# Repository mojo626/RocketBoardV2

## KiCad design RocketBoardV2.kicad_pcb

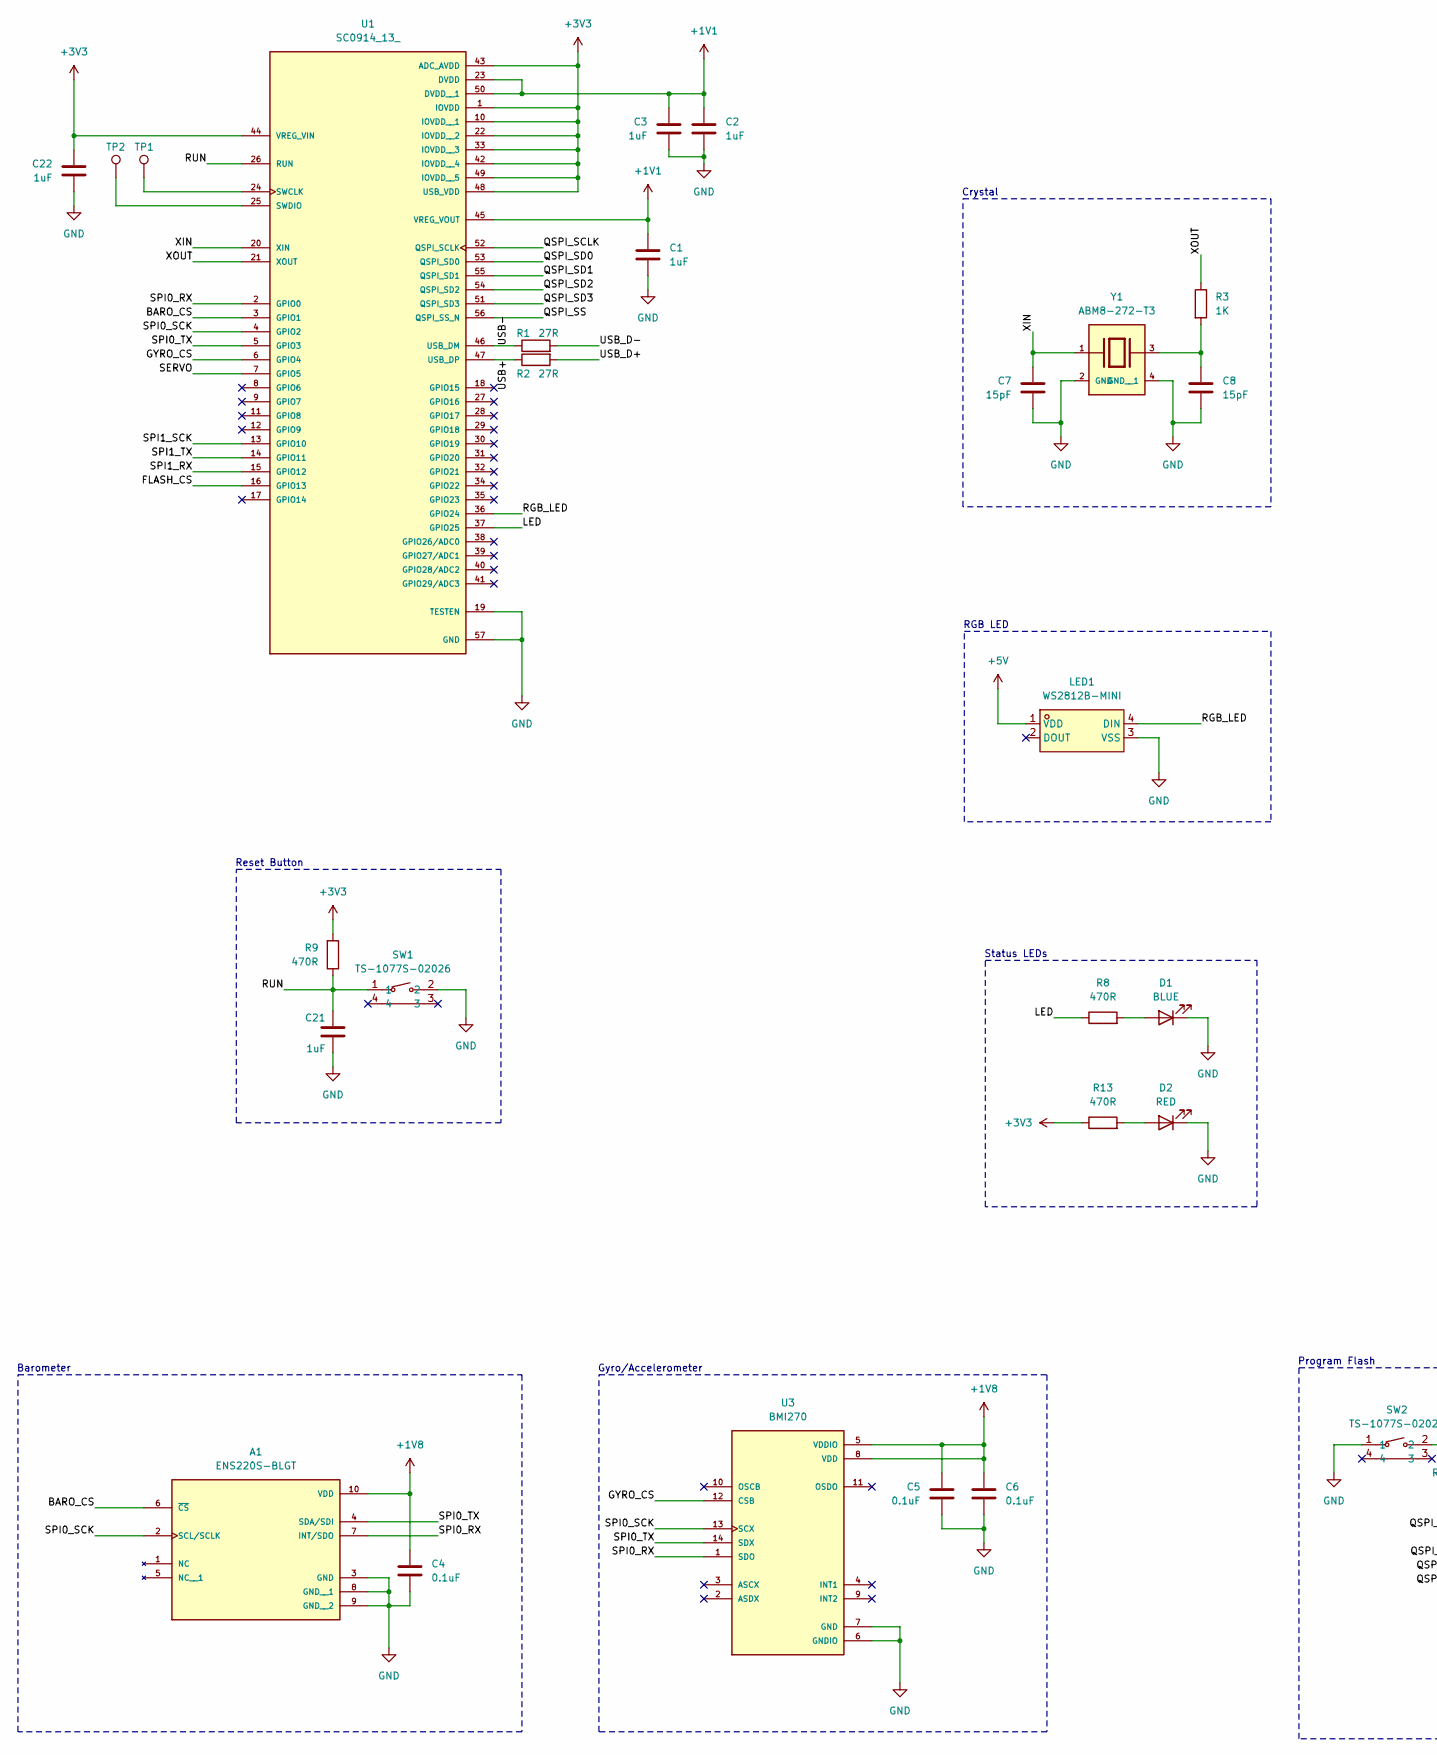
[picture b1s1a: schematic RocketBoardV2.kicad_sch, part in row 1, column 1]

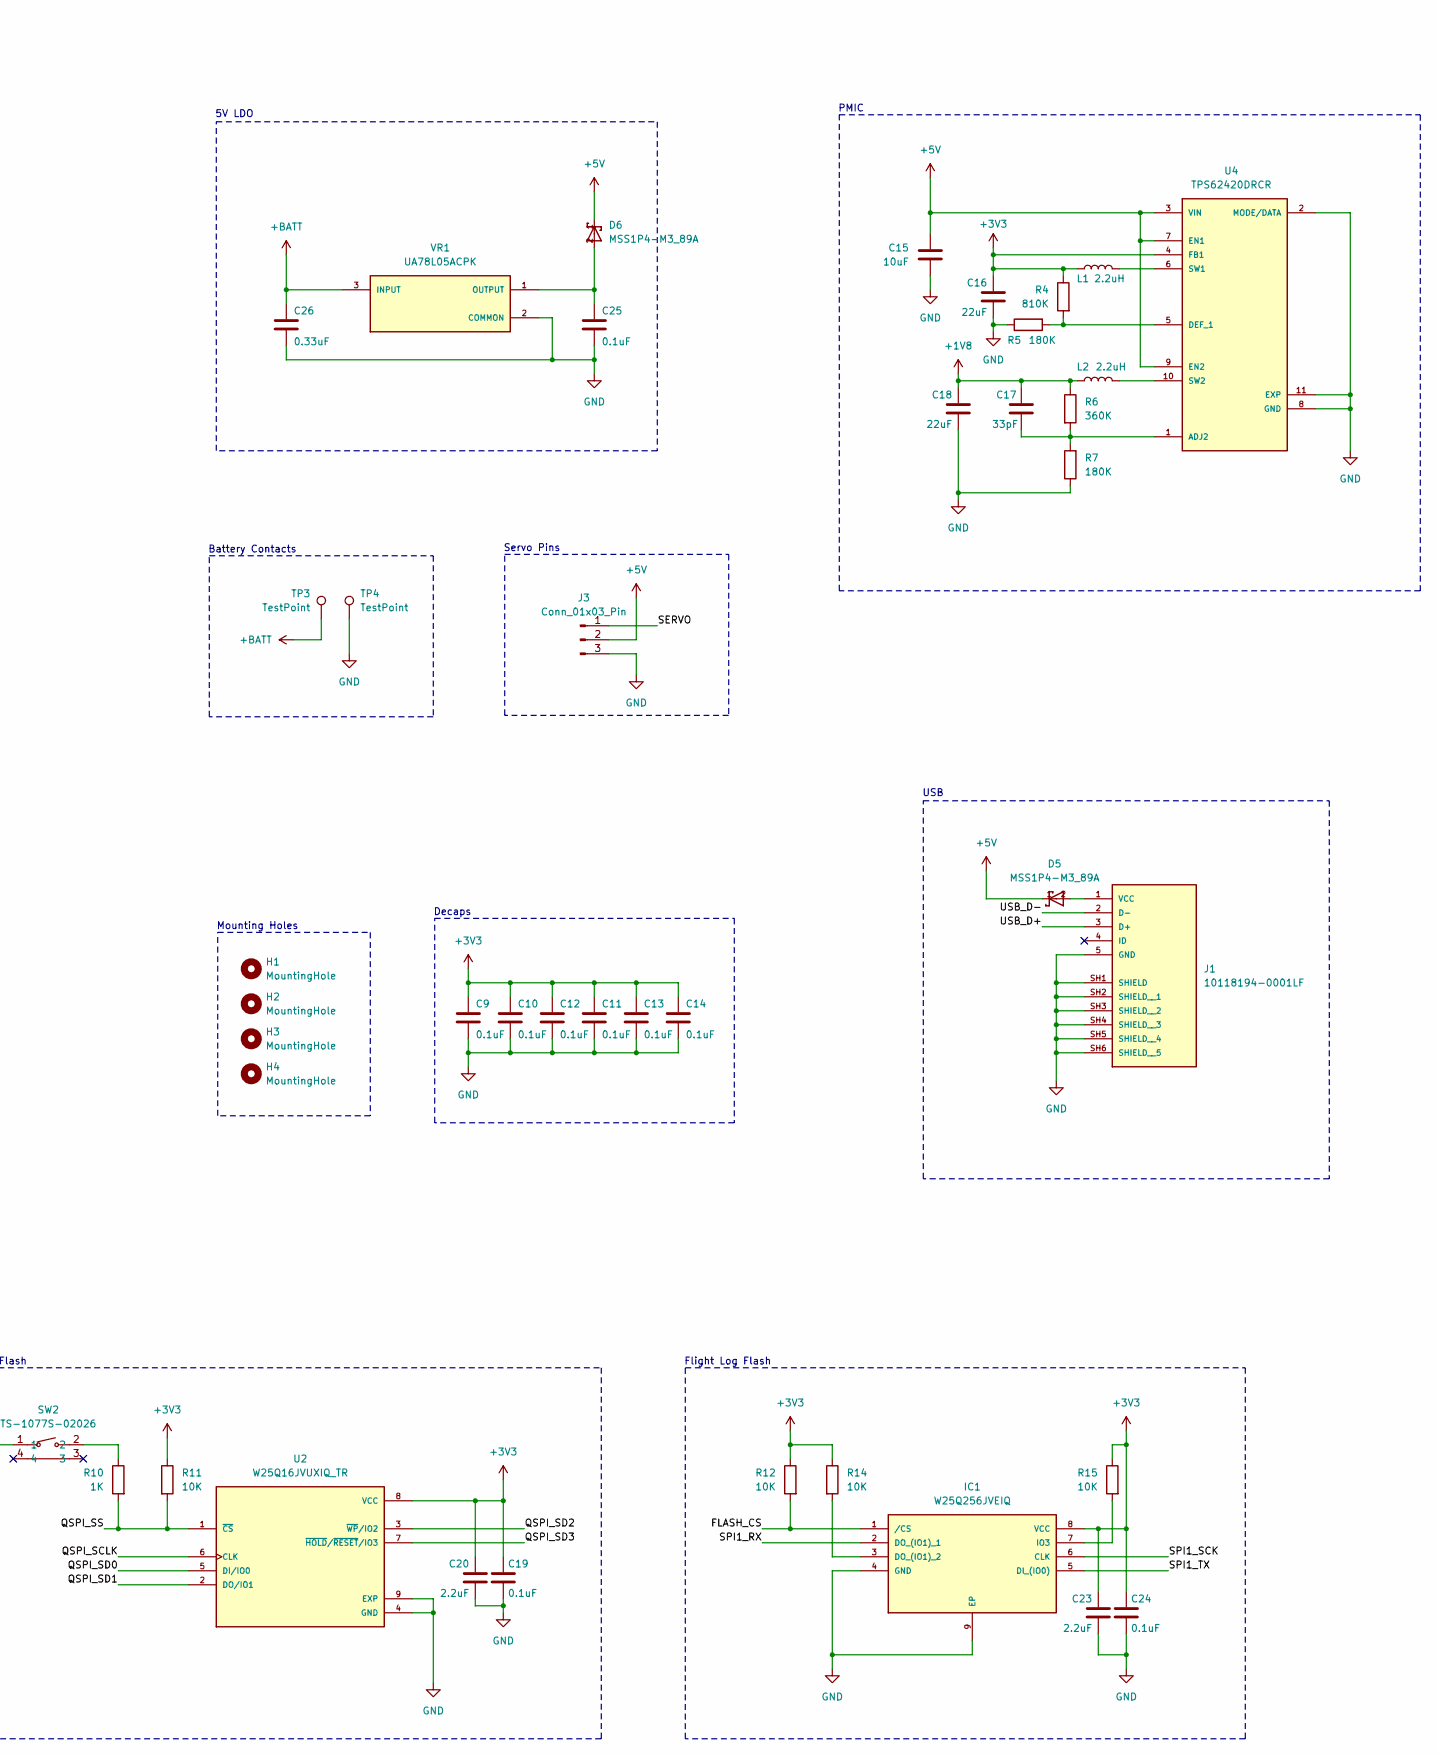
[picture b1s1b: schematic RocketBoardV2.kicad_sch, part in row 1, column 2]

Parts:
A1: ENS220S-BLGT; XDCR_ENS220S-BLGT; PARTREV 1.0
C1, C2, C3, C21, C22: 1uF; C_0402_1005Metric
C4, C5, C6, C9, C10, C11, C12, C13, C14, C19, C24, C25: 0.1uF; C_0402_1005Metric
C7, C8: 15pF; C_0402_1005Metric
C15: 10uF; C_0402_1005Metric
C16, C18: 22uF; C_0402_1005Metric
C17: 33pF; C_0402_1005Metric
C20, C23: 2.2uF; C_0402_1005Metric
C26: 0.33uF; C_0402_1005Metric
D1: BLUE; LED_0402_1005Metric
D2: RED; LED_0402_1005Metric
D5, D6: MSS1P4-M3_89A; DIODE_MSS1P4-M3_89A
H1, H2, H3, H4: MountingHole; MountingHole_3mm
IC1: W25Q256JVEIQ; SON127P800X600X80-9N; MOUSER_PART_NUMBER 454-W25Q256JVEIQ
J1: 10118194-0001LF; AMPHENOL_10118194-0001LF; PARTREV D
J3: Conn_01x03_Pin; PinHeader_1x03_P2.54mm_Horizontal
L1, L2: 2.2uH; L_0402_1005Metric
LED1: WS2812B-MINI; LED-SMD_4P-L3.5-W3.5-TL_WS2812B; LCSC Part C527089
R1, R2: 27R; R_0402_1005Metric
R3, R10: 1K; R_0402_1005Metric
R4: 810K; R_0402_1005Metric
R5, R7: 180K; R_0402_1005Metric
R6: 360K; R_0402_1005Metric
R8, R9, R13: 470R; R_0402_1005Metric
R11, R12, R14, R15: 10K; R_0402_1005Metric
SW1, SW2: TS-1077S-02026; SW-SMD_L3.1-W3.1-P2.20-LS4.0; LCSC Part C455261
TP1, TP2: TestPoint; TestPoint_Pad_1.0x1.0mm
TP3, TP4: TestPoint; TestPoint_Pad_3.0x3.0mm
U1: SC0914_13_; QFN40P700X700X90-57N; PARTREV 2.2
U2: W25Q16JVUXIQ_TR; IC_W25Q16JVUXIQ_TR; PARTREV H
U3: BMI270; XDCR_BMI270
U4: TPS62420DRCR; IC_TPS62420DRCR; PARTREV D
VR1: UA78L05ACPK; VREG_UA78L05ACPK; PARTREV V
Y1: ABM8-272-T3; XTAL_ABM8-272-T3; PARTREV 07-29-20

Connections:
+1V1: C1.1, C2.1, C3.1, U1.23 (DVDD), U1.45 (VREG_VOUT), U1.50 (DVDD__1)
+1V8: A1.10 (VDD), C4.1, C5.1, C6.1, C17.1, C18.1, L2.1, R6.1, U3.5 (VDDIO), U3.8 (VDD)
+3V3: C9.1, C10.1, C11.1, C12.1, C13.1, C14.1, C16.1, C19.1, C20.1, C22.1, C23.1, C24.1, IC1.8 (VCC), L1.1, R4.1, R9.2, R11.1, R12.1, R13.1, R14.1, R15.1, U1.1 (IOVDD), U1.10 (IOVDD__1), U1.22 (IOVDD__2), U1.33 (IOVDD__3), U1.42 (IOVDD__4), U1.43 (ADC_AVDD), U1.44 (VREG_VIN), U1.48 (USB_VDD), U1.49 (IOVDD__5), U2.8 (VCC), U4.4 (FB1)
+5V: C15.1, D5.1, D6.1, J3.2, LED1.1 (VDD), U4.3 (VIN), U4.7 (EN1), U4.9 (EN2)
+BATT: C26.1, TP3.1, VR1.3 (INPUT)
/BARO_CS: A1.6 (~CS), U1.3 (GPIO1)
/FLASH_CS: IC1.1 (/CS), R12.2, U1.16 (GPIO13)
/GYRO_CS: U1.6 (GPIO4), U3.12 (CSB)
/LED: R8.1, U1.37 (GPIO25)
/QSPI_SCLK: U1.52 (QSPI_SCLK), U2.6 (CLK)
/QSPI_SD0: U1.53 (QSPI_SD0), U2.5 (DI/IO0)
/QSPI_SD1: U1.55 (QSPI_SD1), U2.2 (DO/IO1)
/QSPI_SD2: U1.54 (QSPI_SD2), U2.3 (~WP/IO2)
/QSPI_SD3: U1.51 (QSPI_SD3), U2.7 (~HOLD/~RESET/IO3)
/QSPI_SS: R10.2, R11.2, U1.56 (QSPI_SS_N), U2.1 (~CS)
/RGB_LED: LED1.4 (DIN), U1.36 (GPIO24)
/RUN: C21.1, R9.1, SW1.1, U1.26 (RUN)
/SERVO: J3.1, U1.7 (GPIO5)
/SPI0_RX: A1.7 (INT/SDO), U1.2 (GPIO0), U3.1 (SDO)
/SPI0_SCK: A1.2 (SCL/SCLK), U1.4 (GPIO2), U3.13 (SCX)
/SPI0_TX: A1.4 (SDA/SDI), U1.5 (GPIO3), U3.14 (SDX)
/SPI1_RX: IC1.2 (DO_(IO1)_1), U1.15 (GPIO12)
/SPI1_SCK: IC1.6 (CLK), U1.13 (GPIO10)
/SPI1_TX: IC1.5 (DI_(IO0)), U1.14 (GPIO11)
/USB+: R2.1, U1.47 (USB_DP)
/USB-: R1.1, U1.46 (USB_DM)
/USB_D+: J1.3 (D+), R2.2
/USB_D-: J1.2 (D-), R1.2
/XIN: C7.1, U1.20 (XIN), Y1.1
/XOUT: R3.1, U1.21 (XOUT)
GND: A1.3 (GND), A1.8 (GND__1), A1.9 (GND__2), C1.2, C2.2, C3.2, C4.2, C5.2, C6.2, C7.2, C8.2, C9.2, C10.2, C11.2, C12.2, C13.2, C14.2, C15.2, C16.2, C18.2, C19.2, C20.2, C21.2, C22.2, C23.2, C24.2, C25.2, C26.2, D1.1 (K), D2.1 (K), IC1.4 (GND), IC1.9 (EP), J1.5 (GND), J1.SH1 (SHIELD), J1.SH2 (SHIELD__1), J1.SH3 (SHIELD__2), J1.SH4 (SHIELD__3), J1.SH5 (SHIELD__4), J1.SH6 (SHIELD__5), J3.3, LED1.3 (VSS), R5.1, R7.1, SW1.2, SW2.1, TP4.1, U1.19 (TESTEN), U1.57 (GND), U2.4 (GND), U2.9 (EXP), U3.6 (GNDIO), U3.7 (GND), U4.2 (MODE/DATA), U4.8 (GND), U4.11 (EXP), U4.12, U4.13, U4.14, U4.15, VR1.2 (COMMON), Y1.2 (GND), Y1.4 (GND__1)
unnamed: C8.1, R3.2, Y1.3
unnamed: D1.2 (A), R8.2
unnamed: D2.2 (A), R13.2
unnamed: IC1.3 (DO_(IO1)_2), R14.2
unnamed: IC1.7 (IO3), R15.2
unnamed: D5.2, J1.1 (VCC)
unnamed: R10.1, SW2.2
unnamed: TP1.1, U1.24 (SWCLK)
unnamed: TP2.1, U1.25 (SWDIO)
unnamed: C17.2, R6.2, R7.2, U4.1 (ADJ2)
unnamed: R4.2, R5.2, U4.5 (DEF_1)
unnamed: L1.2, U4.6 (SW1)
unnamed: L2.2, U4.10 (SW2)
unnamed: C25.1, D6.2, VR1.1 (OUTPUT)

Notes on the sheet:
Battery Contacts
Gyro/Accelerometer
5V LDO
Decaps
RGB LED
PMIC
Mounting Holes
Flight Log Flash
Servo Pins
Barometer
Reset Button
USB
Program Flash
Crystal
Status LEDs

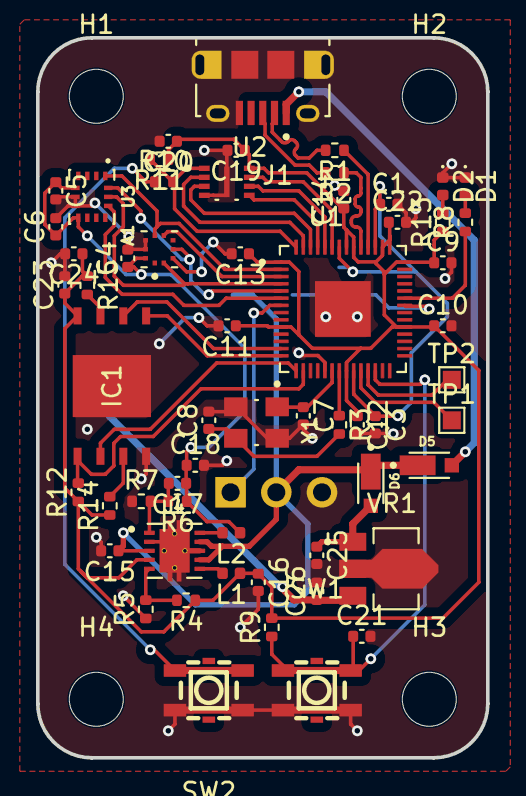
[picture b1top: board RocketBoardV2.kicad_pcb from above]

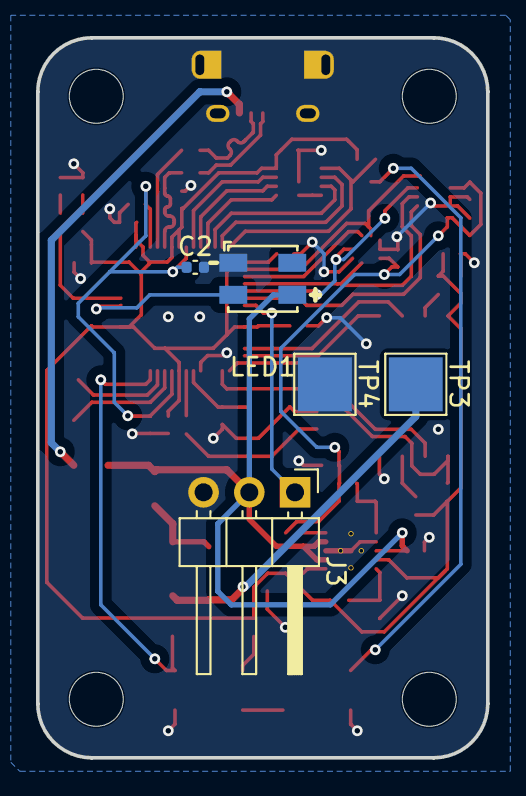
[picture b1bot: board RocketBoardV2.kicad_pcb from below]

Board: 2 copper layers, 25.0 x 40.0 mm, 68 parts (5 on the bottom side), 45 nets.

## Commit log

2025-07-25 created Kicad project
2025-07-25 added main components
2025-07-26 started routing
2025-07-26 added PMIC
2025-07-26 some more power changes
2025-07-27 changed flash, power changes
2025-07-27 organized schematic
2025-07-27 basic layout
2025-07-27 more finalized layout, placed C + R
2025-07-28 starting to route
2025-07-28 initial routing done
